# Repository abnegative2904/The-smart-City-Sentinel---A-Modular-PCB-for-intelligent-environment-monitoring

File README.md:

# The Smart City Sentinel - A Modular PCB for Intelligent Environment Monitoring

##Footprints are missing for some components

## 1. Power Supply:
   - The system is powered by a solar panel and a rechargeable battery, managed by a TP4056 module.
   - A voltage booster ensures components needing 5V are powered correctly.
   - The ESP32-C3 monitors the battery level. When the battery is low, it charges through the solar panel.

## 2. Data Collection:
   - *Air Quality:* The MQ-135 sensor detects harmful gases.
   - *Temperature, Humidity, and Pressure:* The BME280 and DHT11 sensors gather environmental data.
   - *Sound Levels:* A sound sensor measures ambient noise.
   - *Dust and Particulate Matter:* A dust sensor monitors air quality.
   - *Additional Sensors:* Hall effect, water flow, soil moisture, and rain sensors provide more data.

## 3. Data Processing:
   - The ESP32-C3 processes data from all sensors. It uses the DS3231 RTC module to timestamp the data for accurate logging.

## 4. Display and Output:
   - An OLED display shows real-time data for easy monitoring.
   - A relay module can control external devices based on sensor readings (e.g., turning on a fan if air quality is poor).

## 5. Communication:
   - I2C communication is used for the OLED display, RTC, and BME280 sensor.
   - The system can send data to a server or cloud for remote monitoring and analysis.

This setup provides a comprehensive solution for monitoring environmental conditions, making it ideal for applications like smart agriculture, home automation, and environmental research.

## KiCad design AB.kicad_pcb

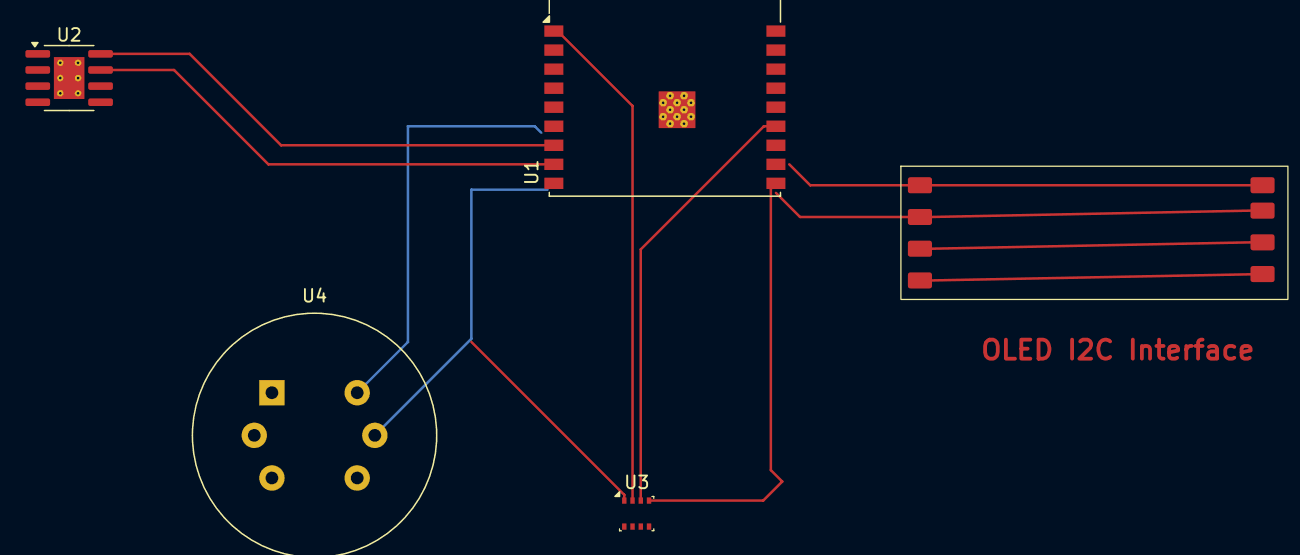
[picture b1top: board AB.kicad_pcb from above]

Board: 2 copper layers, 5 parts (0 on the bottom side), 8 nets.

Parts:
U1: ESP32-C3-WROOM-02
U2: TP4056-42-ESOP8; SOIC-8-1EP_3.9x4.9mm_P1.27mm_EP2.41x3.3mm_ThermalVias
U3: BME280; Bosch_LGA-8_2.5x2.5mm_P0.65mm_ClockwisePinNumbering
U4: MQ-135_edited; MQ-6
U5: Untitled

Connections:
unnamed: U1.9 (GND), U1.19 (GND), U3.1 (GND), U3.7 (GND), U4.5 (VH-)
unnamed: U1.1 (3V3), U3.2 (CSB), U3.6 (VDDIO), U3.8 (VDD)
unnamed: U1.6 (IO7), U4.6 (A1)
unnamed: U1.7 (IO8), U2.8 (CE)
unnamed: U1.8 (IO9), U2.7 (~CHRG)
unnamed: U1.10 (IO10), U3.4 (SCK)
unnamed: U1.13 (IO18), U3.3 (SDI)
SOLAR A-: U2.1 (TEMP), U2.3 (GND)
